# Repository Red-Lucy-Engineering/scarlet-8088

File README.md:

# "scarlet-8088": Intel 8088-based ATX motherboard

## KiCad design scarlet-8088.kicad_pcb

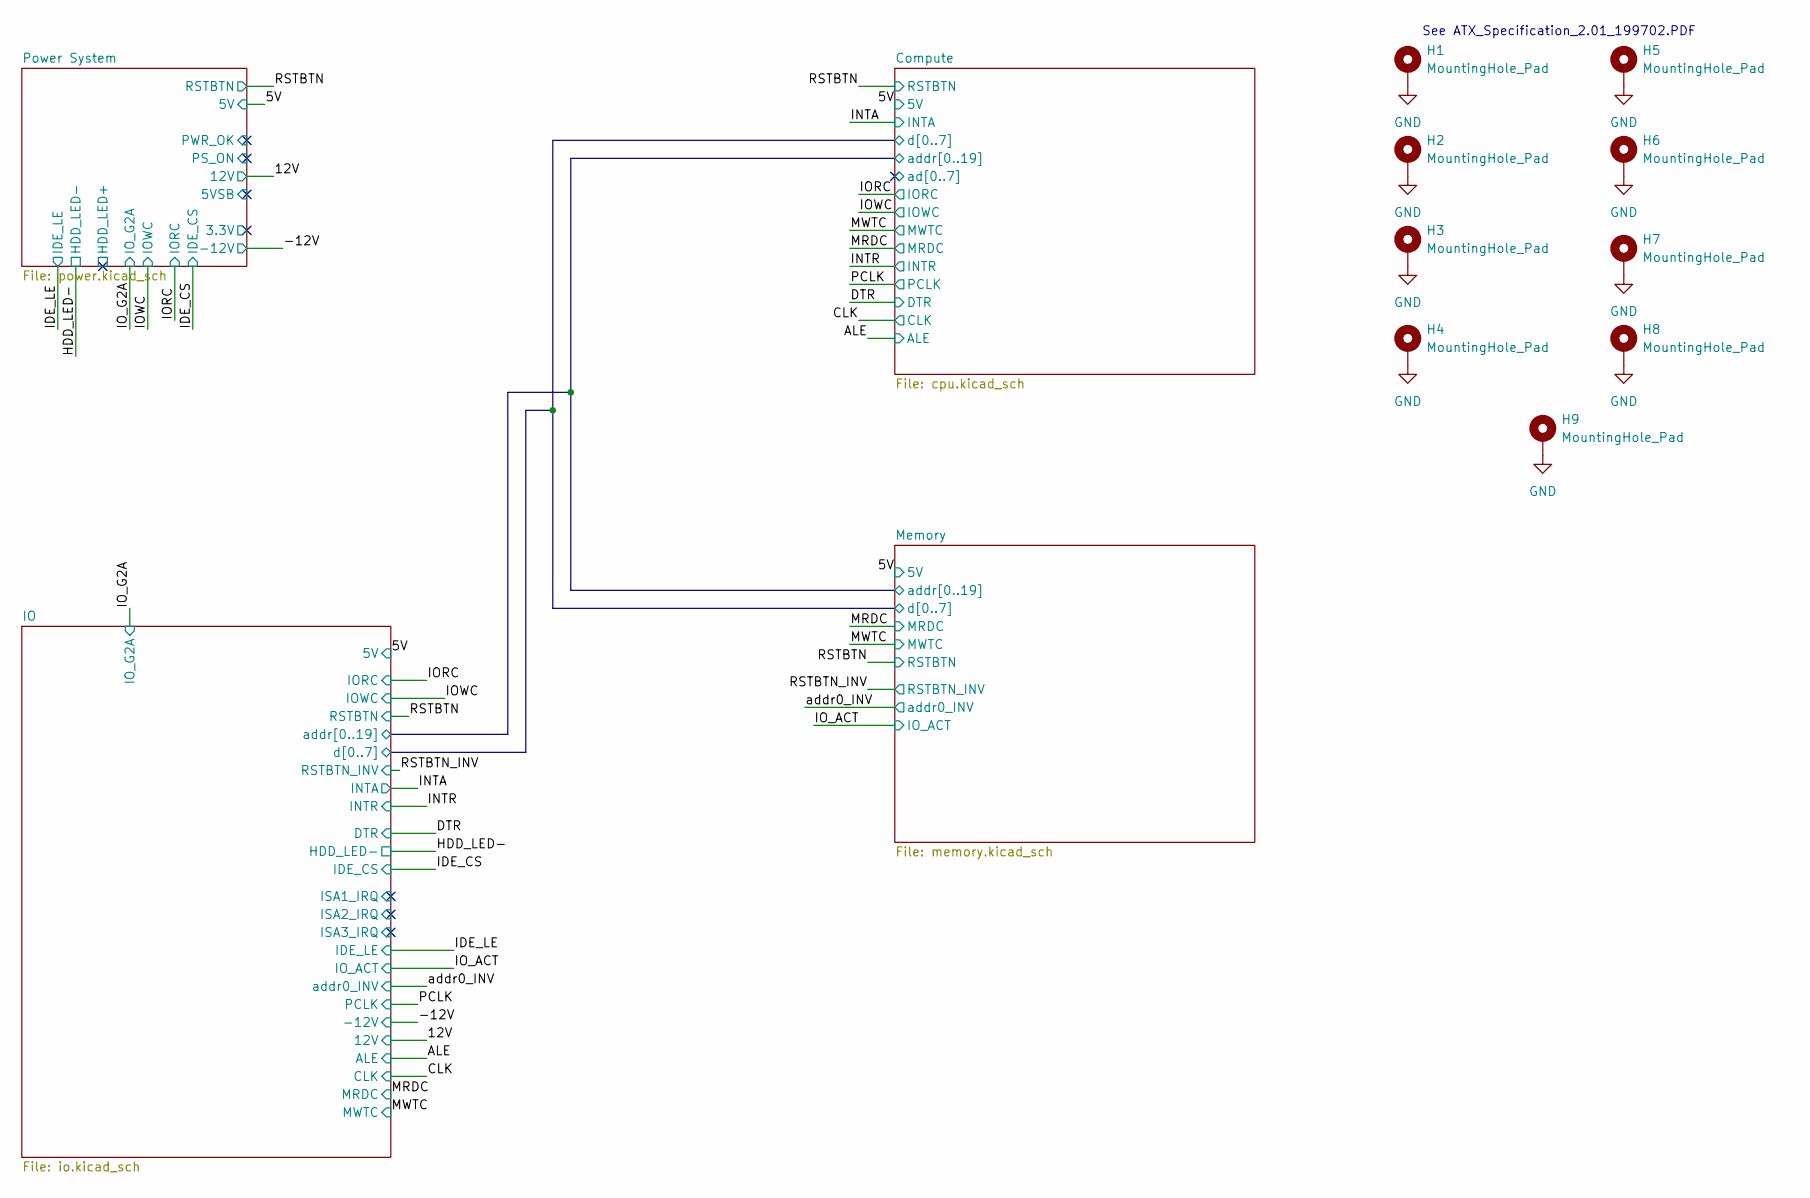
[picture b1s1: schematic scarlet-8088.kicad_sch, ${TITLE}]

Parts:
H1, H2, H3, H4, H5, H6, H7, H8, H9: MountingHole_Pad; MountingHole_3.2mm_M3_Pad_TopBottom

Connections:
GND: H1.1 (1_1), H2.1 (1_1), H3.1 (1_1), H4.1 (1_1), H5.1 (1_1), H6.1 (1_1), H7.1 (1_1), H8.1 (1_1), H9.1 (1_1); also elsewhere on the board

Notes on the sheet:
See ATX_Specification_2.01_199702.PDF

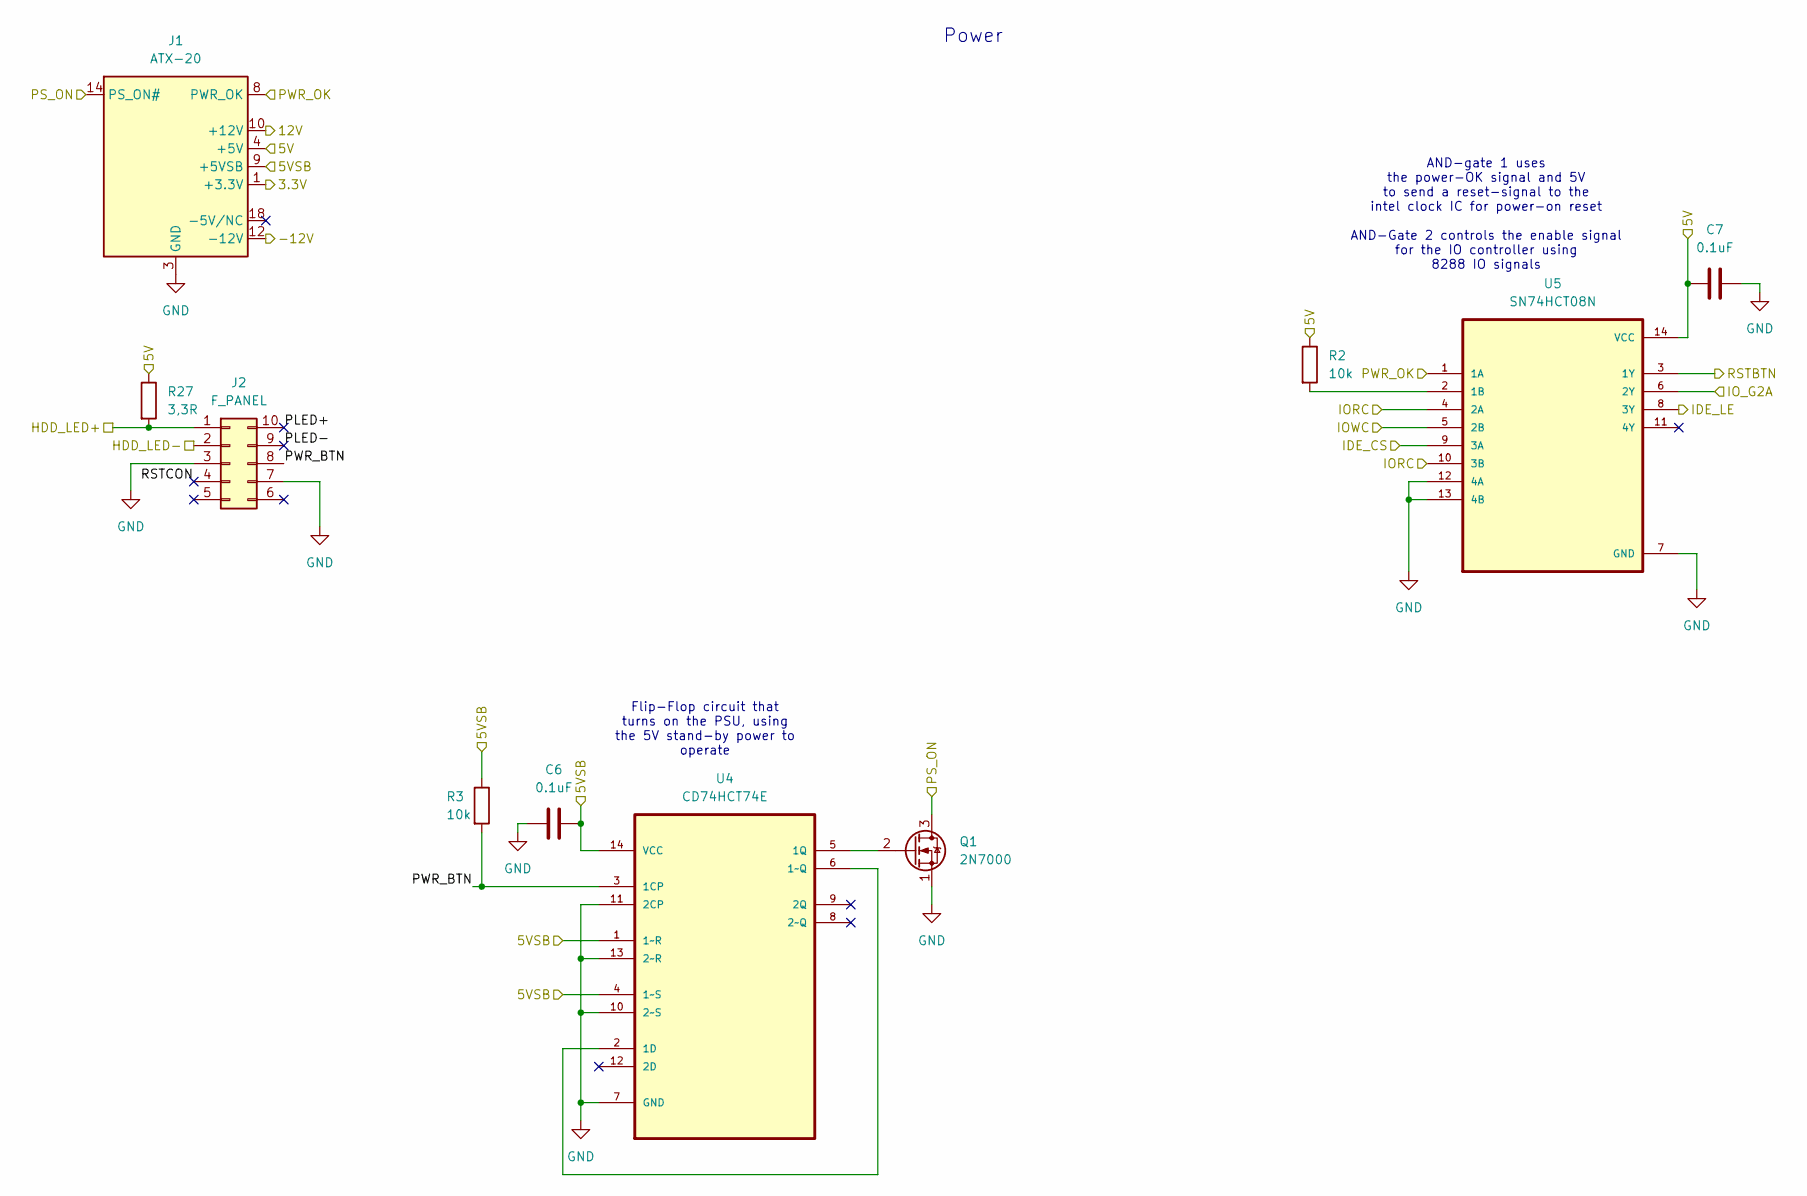
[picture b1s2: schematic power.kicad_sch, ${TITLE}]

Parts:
C6, C7: 0.1uF; C_Disc_D3.0mm_W1.6mm_P2.50mm
J1: ATX-20; Molex_Mini-Fit_Jr_5566-20A_2x10_P4.20mm_Vertical
J2: F_PANEL; PinHeader_2x05_P2.54mm_Vertical
Q1: 2N7000; TO-92_Inline
R2, R3: 10k; R_Axial_DIN0204_L3.6mm_D1.6mm_P5.08mm_Horizontal
R27: 3,3R; R_Axial_DIN0204_L3.6mm_D1.6mm_P5.08mm_Horizontal
U4: CD74HCT74E; DIP254P762X508-14; MPN CD74HCT74E
U5: SN74HCT08N; DIP794W45P254L1969H508Q14

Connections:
/5V: C7.1, J1.4 (+5V), J1.6 (+5V), J1.19 (+5V), J1.20 (+5V), R2.1, R27.1, U5.14 (VCC); also elsewhere on the board
/12V: J1.10 (+12V); also elsewhere on the board
/-12V: J1.12 (-12V); also elsewhere on the board
/HDD_LED-: J2.2; also elsewhere on the board
/IDE_CS: U5.9 (3A); also elsewhere on the board
/IDE_LE: U5.8 (3Y); also elsewhere on the board
/IORC: U5.4 (2A), U5.10 (3B); also elsewhere on the board
/IOWC: U5.5 (2B); also elsewhere on the board
/IO_G2A: U5.6 (2Y); also elsewhere on the board
/Power System/5VSB: C6.2, J1.9 (+5VSB), R3.1, U4.1 (1~R), U4.4 (1~S), U4.14 (VCC)
/Power System/HDD_LED+: J2.1, R27.2
/Power System/PLED+: J2.10
/Power System/PLED-: J2.9
/Power System/PS_ON: J1.14 (PS_ON#), Q1.3 (D)
/Power System/PWR_BTN: J2.8, R3.2, U4.3 (1CP)
/Power System/PWR_OK: J1.8 (PWR_OK), U5.1 (1A)
/Power System/RSTCON: J2.4
/RSTBTN: U5.3 (1Y); also elsewhere on the board
GND: C6.1, C7.2, J1.3 (GND), J1.5 (GND), J1.7 (GND), J1.13 (GND), J1.15 (GND), J1.16 (GND), J1.17 (GND), J2.3, J2.7, Q1.1 (S), U4.7 (GND), U4.10 (2~S), U4.11 (2CP), U4.13 (2~R), U5.7 (GND), U5.12 (4A), U5.13 (4B); also elsewhere on the board
unnamed: Q1.2 (G), U4.5 (1Q)
unnamed: U4.2 (1D), U4.6 (1~Q)
unnamed: R2.2, U5.2 (1B)

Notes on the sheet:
Power
AND-gate 1 uses the power-OK signal and 5V to send a reset-signal to the intel clock IC for power-on reset AND-Gate 2 controls the enable signal for the IO controller using 8288 IO signals
Flip-Flop circuit that turns on the PSU, using the 5V stand-by power to operate

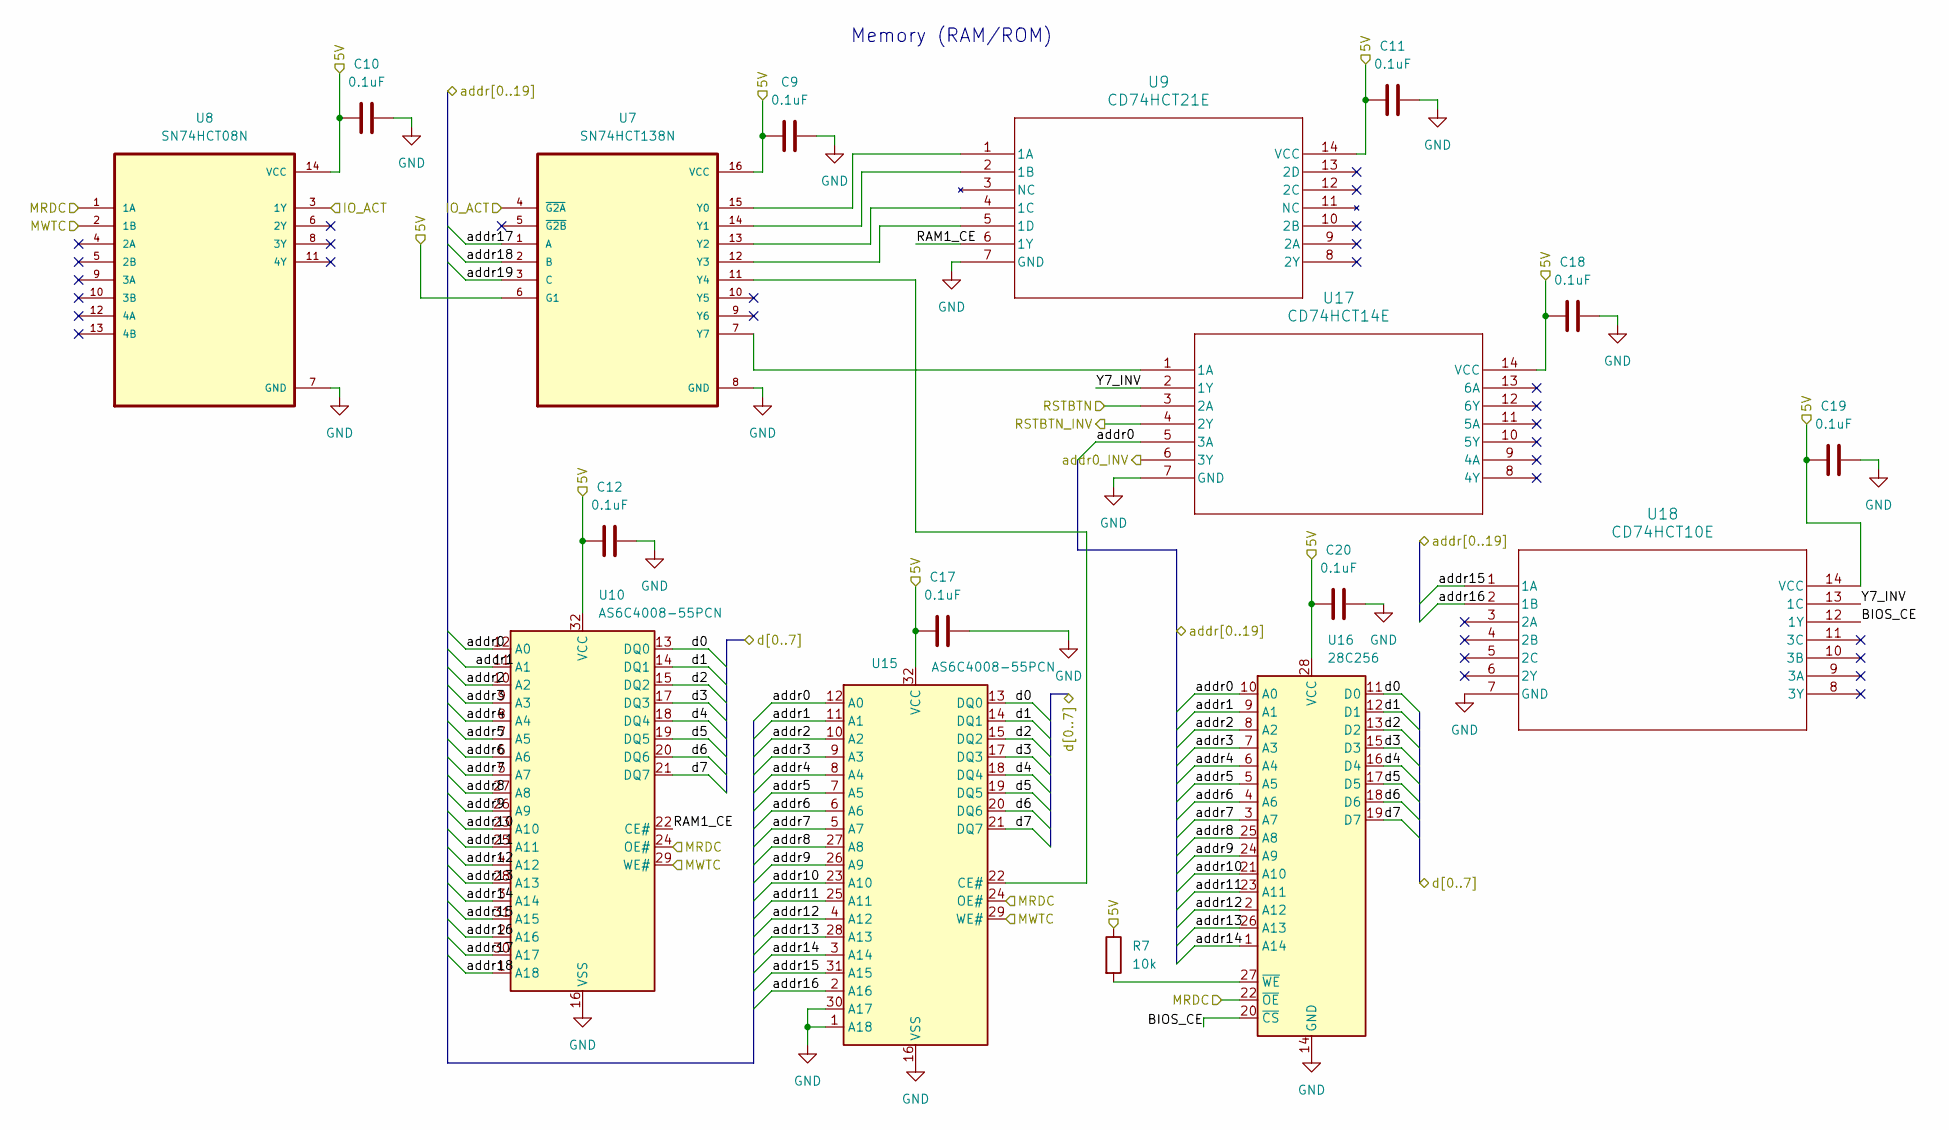
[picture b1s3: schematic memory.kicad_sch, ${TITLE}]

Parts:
C9, C10, C11, C12, C17, C18, C19, C20: 0.1uF; C_Disc_D3.0mm_W1.6mm_P2.50mm
R7: 10k; R_Axial_DIN0204_L3.6mm_D1.6mm_P5.08mm_Horizontal
U7: SN74HCT138N; DIP794W45P254L1969H508Q16
U8: SN74HCT08N; DIP794W45P254L1969H508Q14
U9: CD74HCT21E; N14
U10, U15: AS6C4008-55PCN; DIP-32_W15.24mm_Socket
U16: 28C256; DIP-28_W15.24mm_Socket
U17: CD74HCT14E
U18: CD74HCT10E; N14

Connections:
/5V: C9.2, C10.1, C11.2, C12.1, C17.1, C18.2, C19.2, C20.1, R7.1, U7.6 (G1), U7.16 (VCC), U8.14 (VCC), U9.14 (VCC), U10.32 (VCC), U15.32 (VCC), U16.28 (VCC), U17.14 (VCC), U18.14 (VCC); also elsewhere on the board
/Compute/addr0: U10.12 (A0), U15.12 (A0), U16.10 (A0), U17.5 (3A); also elsewhere on the board
/Compute/addr1: U10.11 (A1), U15.11 (A1), U16.9 (A1); also elsewhere on the board
/Compute/addr2: U10.10 (A2), U15.10 (A2), U16.8 (A2); also elsewhere on the board
/Compute/addr3: U10.9 (A3), U15.9 (A3), U16.7 (A3); also elsewhere on the board
/Compute/addr4: U10.8 (A4), U15.8 (A4), U16.6 (A4); also elsewhere on the board
/Compute/addr5: U10.7 (A5), U15.7 (A5), U16.5 (A5); also elsewhere on the board
/Compute/addr6: U10.6 (A6), U15.6 (A6), U16.4 (A6); also elsewhere on the board
/Compute/addr7: U10.5 (A7), U15.5 (A7), U16.3 (A7); also elsewhere on the board
/Compute/addr8: U10.27 (A8), U15.27 (A8), U16.25 (A8); also elsewhere on the board
/Compute/addr9: U10.26 (A9), U15.26 (A9), U16.24 (A9); also elsewhere on the board
/Compute/addr10: U10.23 (A10), U15.23 (A10), U16.21 (A10); also elsewhere on the board
/Compute/addr11: U10.25 (A11), U15.25 (A11), U16.23 (A11); also elsewhere on the board
/Compute/addr12: U10.4 (A12), U15.4 (A12), U16.2 (A12); also elsewhere on the board
/Compute/addr13: U10.28 (A13), U15.28 (A13), U16.26 (A13); also elsewhere on the board
/Compute/addr14: U10.3 (A14), U15.3 (A14), U16.1 (A14); also elsewhere on the board
/Compute/addr15: U10.31 (A15), U15.31 (A15), U18.1 (1A); also elsewhere on the board
/Compute/addr16: U10.2 (A16), U15.2 (A16), U18.2 (1B); also elsewhere on the board
/Compute/addr17: U7.1 (A), U10.30 (A17); also elsewhere on the board
/Compute/addr18: U7.2 (B), U10.1 (A18); also elsewhere on the board
/Compute/addr19: U7.3 (C); also elsewhere on the board
/Compute/d0: U10.13 (DQ0), U15.13 (DQ0), U16.11 (D0); also elsewhere on the board
/Compute/d1: U10.14 (DQ1), U15.14 (DQ1), U16.12 (D1); also elsewhere on the board
/Compute/d2: U10.15 (DQ2), U15.15 (DQ2), U16.13 (D2); also elsewhere on the board
/Compute/d3: U10.17 (DQ3), U15.17 (DQ3), U16.15 (D3); also elsewhere on the board
/Compute/d4: U10.18 (DQ4), U15.18 (DQ4), U16.16 (D4); also elsewhere on the board
/Compute/d5: U10.19 (DQ5), U15.19 (DQ5), U16.17 (D5); also elsewhere on the board
/Compute/d6: U10.20 (DQ6), U15.20 (DQ6), U16.18 (D6); also elsewhere on the board
/Compute/d7: U10.21 (DQ7), U15.21 (DQ7), U16.19 (D7); also elsewhere on the board
/IO_ACT: U7.4 (~G2A), U8.3 (1Y); also elsewhere on the board
/MRDC: U8.1 (1A), U10.24 (OE#), U15.24 (OE#), U16.22 (~OE); also elsewhere on the board
/MWTC: U8.2 (1B), U10.29 (WE#), U15.29 (WE#); also elsewhere on the board
/Memory/BIOS_CE: U16.20 (~CS), U18.12 (1Y)
/Memory/RAM1_CE: U9.6 (1Y), U10.22 (CE#)
/Memory/Y7_INV: U17.2 (1Y), U18.13 (1C)
/RSTBTN: U17.3 (2A); also elsewhere on the board
/RSTBTN_INV: U17.4 (2Y); also elsewhere on the board
/addr0_INV: U17.6 (3Y); also elsewhere on the board
GND: C9.1, C10.2, C11.1, C12.2, C17.2, C18.1, C19.1, C20.2, U7.8 (GND), U8.7 (GND), U9.7 (GND), U10.16 (VSS), U15.1 (A18), U15.16 (VSS), U15.30 (A17), U16.14 (GND), U17.7 (GND), U18.7 (GND); also elsewhere on the board
unnamed: U7.15 (Y0), U9.1 (1A)
unnamed: U7.14 (Y1), U9.2 (1B)
unnamed: U7.13 (Y2), U9.4 (1C)
unnamed: U7.12 (Y3), U9.5 (1D)
unnamed: U7.11 (Y4), U15.22 (CE#)
unnamed: R7.2, U16.27 (~WE)
unnamed: U7.7 (Y7), U17.1 (1A)

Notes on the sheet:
Memory (RAM/ROM)

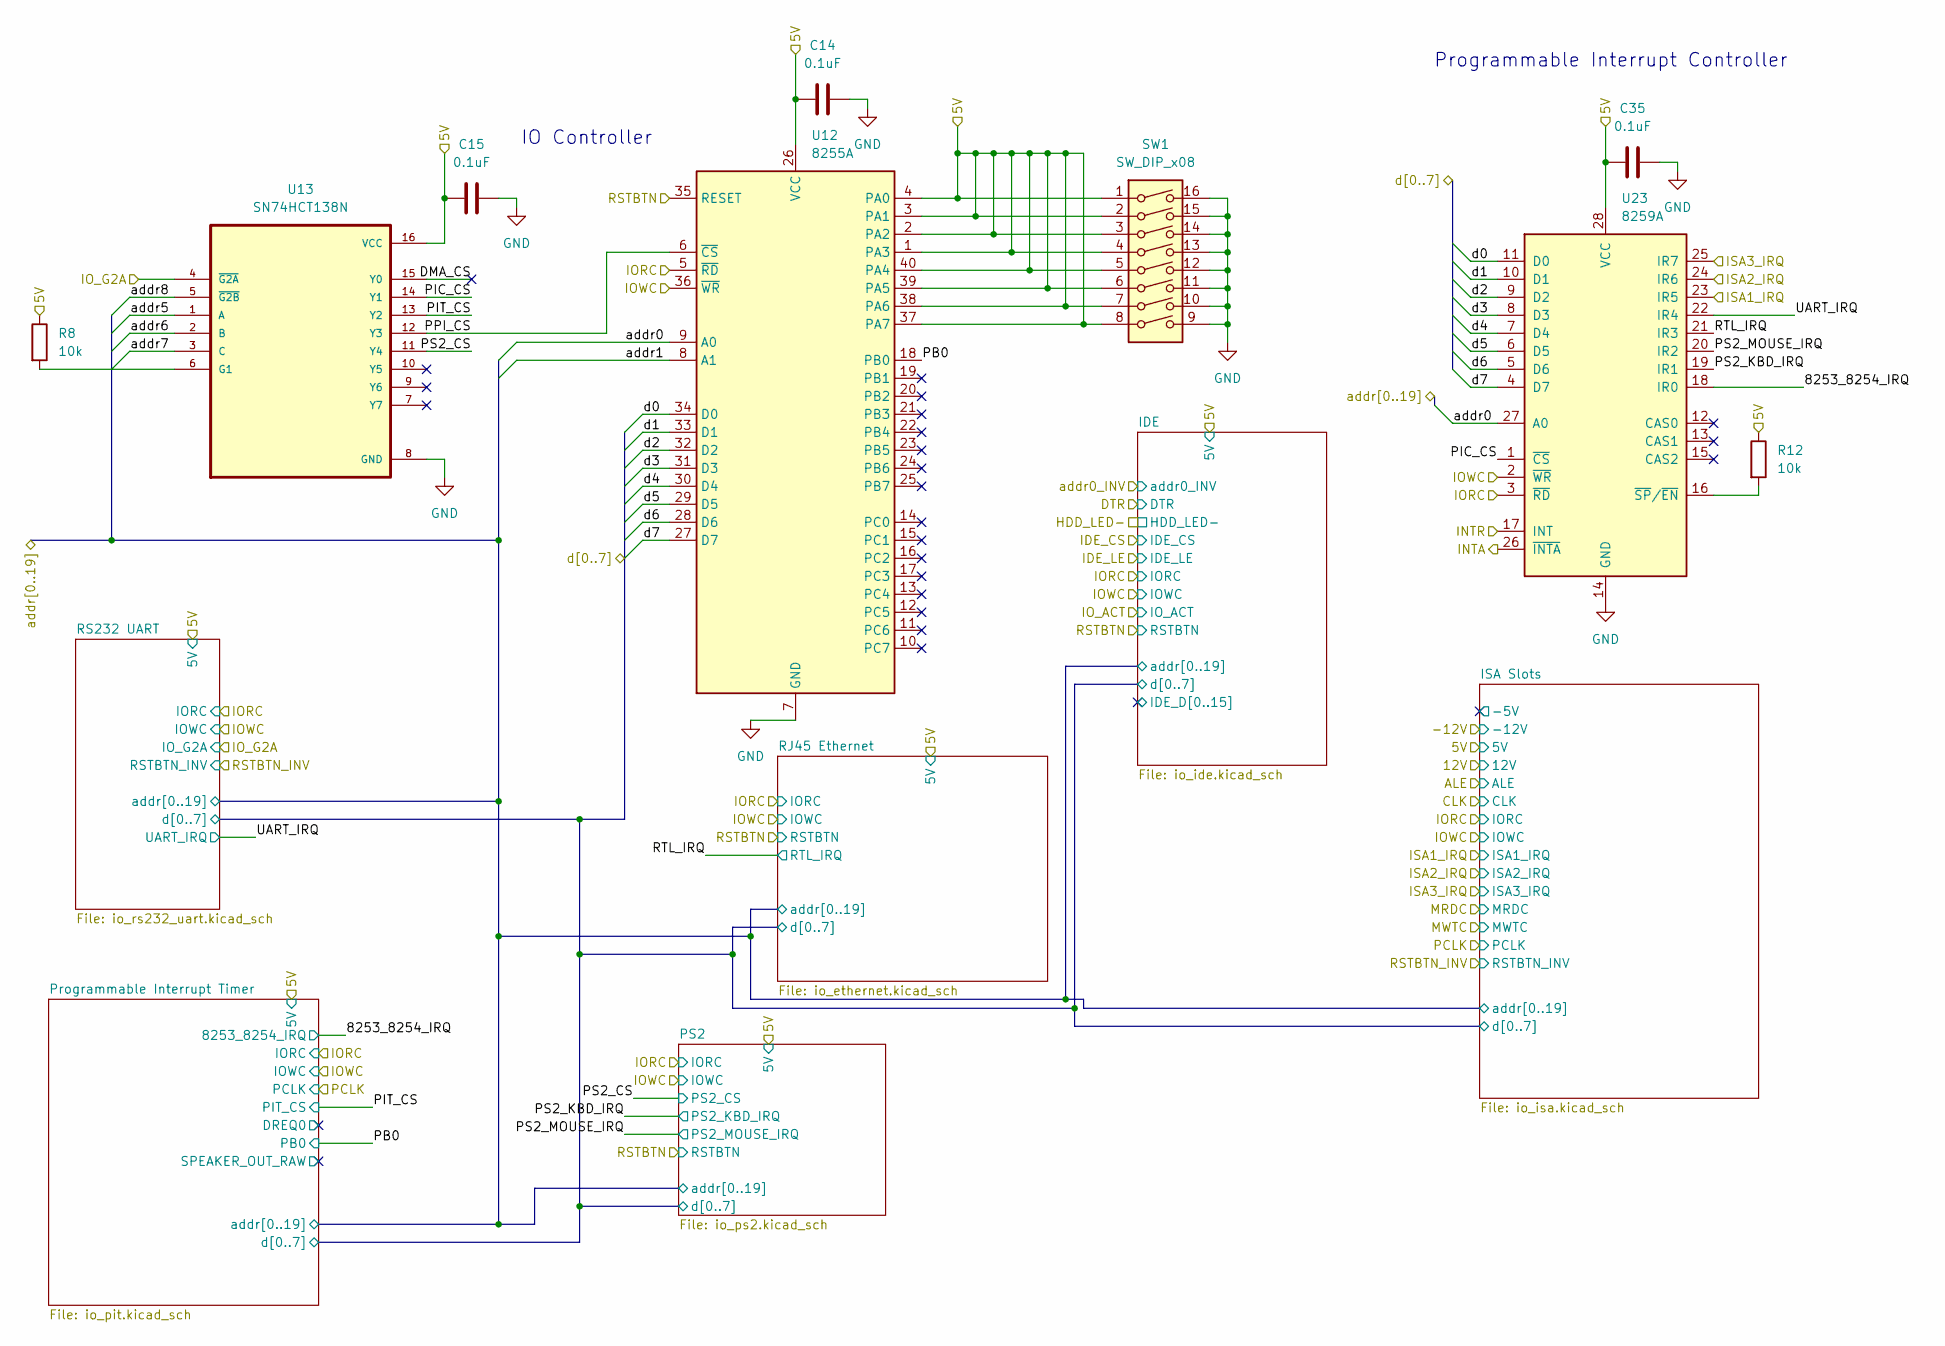
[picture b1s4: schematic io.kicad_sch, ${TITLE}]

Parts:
C14, C15, C35: 0.1uF; C_Disc_D3.0mm_W1.6mm_P2.50mm
R8, R12: 10k; R_Axial_DIN0204_L3.6mm_D1.6mm_P5.08mm_Horizontal
SW1: SW_DIP_x08; SW_DIP_SPSTx08_Piano_10.8x21.88mm_W7.62mm_P2.54mm
U12: 8255A; DIP-40_W15.24mm_Socket
U13: SN74HCT138N; DIP794W45P254L1969H508Q16
U23: 8259A; DIP-28_W15.24mm_Socket

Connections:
/5V: C14.1, C15.1, C35.1, R8.1, R12.1, SW1.1, SW1.2, SW1.3, SW1.4, SW1.5, SW1.6, SW1.7, SW1.8, U12.1 (PA3), U12.2 (PA2), U12.3 (PA1), U12.4 (PA0), U12.26 (VCC), U12.37 (PA7), U12.38 (PA6), U12.39 (PA5), U12.40 (PA4), U13.16 (VCC), U23.28 (VCC); also elsewhere on the board
/Compute/addr0: U12.9 (A0), U23.27 (A0); also elsewhere on the board
/Compute/addr1: U12.8 (A1); also elsewhere on the board
/Compute/addr5: U13.1 (A); also elsewhere on the board
/Compute/addr6: U13.2 (B); also elsewhere on the board
/Compute/addr7: U13.3 (C); also elsewhere on the board
/Compute/addr8: U13.5 (~G2B); also elsewhere on the board
/Compute/d0: U12.34 (D0), U23.11 (D0); also elsewhere on the board
/Compute/d1: U12.33 (D1), U23.10 (D1); also elsewhere on the board
/Compute/d2: U12.32 (D2), U23.9 (D2); also elsewhere on the board
/Compute/d3: U12.31 (D3), U23.8 (D3); also elsewhere on the board
/Compute/d4: U12.30 (D4), U23.7 (D4); also elsewhere on the board
/Compute/d5: U12.29 (D5), U23.6 (D5); also elsewhere on the board
/Compute/d6: U12.28 (D6), U23.5 (D6); also elsewhere on the board
/Compute/d7: U12.27 (D7), U23.4 (D7); also elsewhere on the board
/INTA: U23.26 (~INTA); also elsewhere on the board
/INTR: U23.17 (INT); also elsewhere on the board
/IO/8253_8254_IRQ: U23.18 (IR0); also elsewhere on the board
/IO/DMA_CS: U13.15 (Y0)
/IO/ISA1_IRQ: U23.23 (IR5); also elsewhere on the board
/IO/ISA2_IRQ: U23.24 (IR6); also elsewhere on the board
/IO/ISA3_IRQ: U23.25 (IR7); also elsewhere on the board
/IO/PB0: U12.18 (PB0); also elsewhere on the board
/IO/PIC_CS: U13.14 (Y1), U23.1 (~CS)
/IO/PIT_CS: U13.13 (Y2); also elsewhere on the board
/IO/PPI_CS: U12.6 (~CS), U13.12 (Y3)
/IO/PS2_CS: U13.11 (Y4); also elsewhere on the board
/IO/PS2_KBD_IRQ: U23.19 (IR1); also elsewhere on the board
/IO/PS2_MOUSE_IRQ: U23.20 (IR2); also elsewhere on the board
/IO/RTL_IRQ: U23.21 (IR3); also elsewhere on the board
/IO/UART_IRQ: U23.22 (IR4); also elsewhere on the board
/IORC: U12.5 (~RD), U23.3 (~RD); also elsewhere on the board
/IOWC: U12.36 (~WR), U23.2 (~WR); also elsewhere on the board
/IO_G2A: U13.4 (~G2A); also elsewhere on the board
/RSTBTN: U12.35 (RESET); also elsewhere on the board
GND: C14.2, C15.2, C35.2, SW1.9, SW1.10, SW1.11, SW1.12, SW1.13, SW1.14, SW1.15, SW1.16, U12.7 (GND), U13.8 (GND), U23.14 (GND); also elsewhere on the board
unnamed: R8.2, U13.6 (G1)
unnamed: R12.2, U23.16 (~SP/~EN)

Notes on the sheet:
Programmable Interrupt Controller
IO Controller

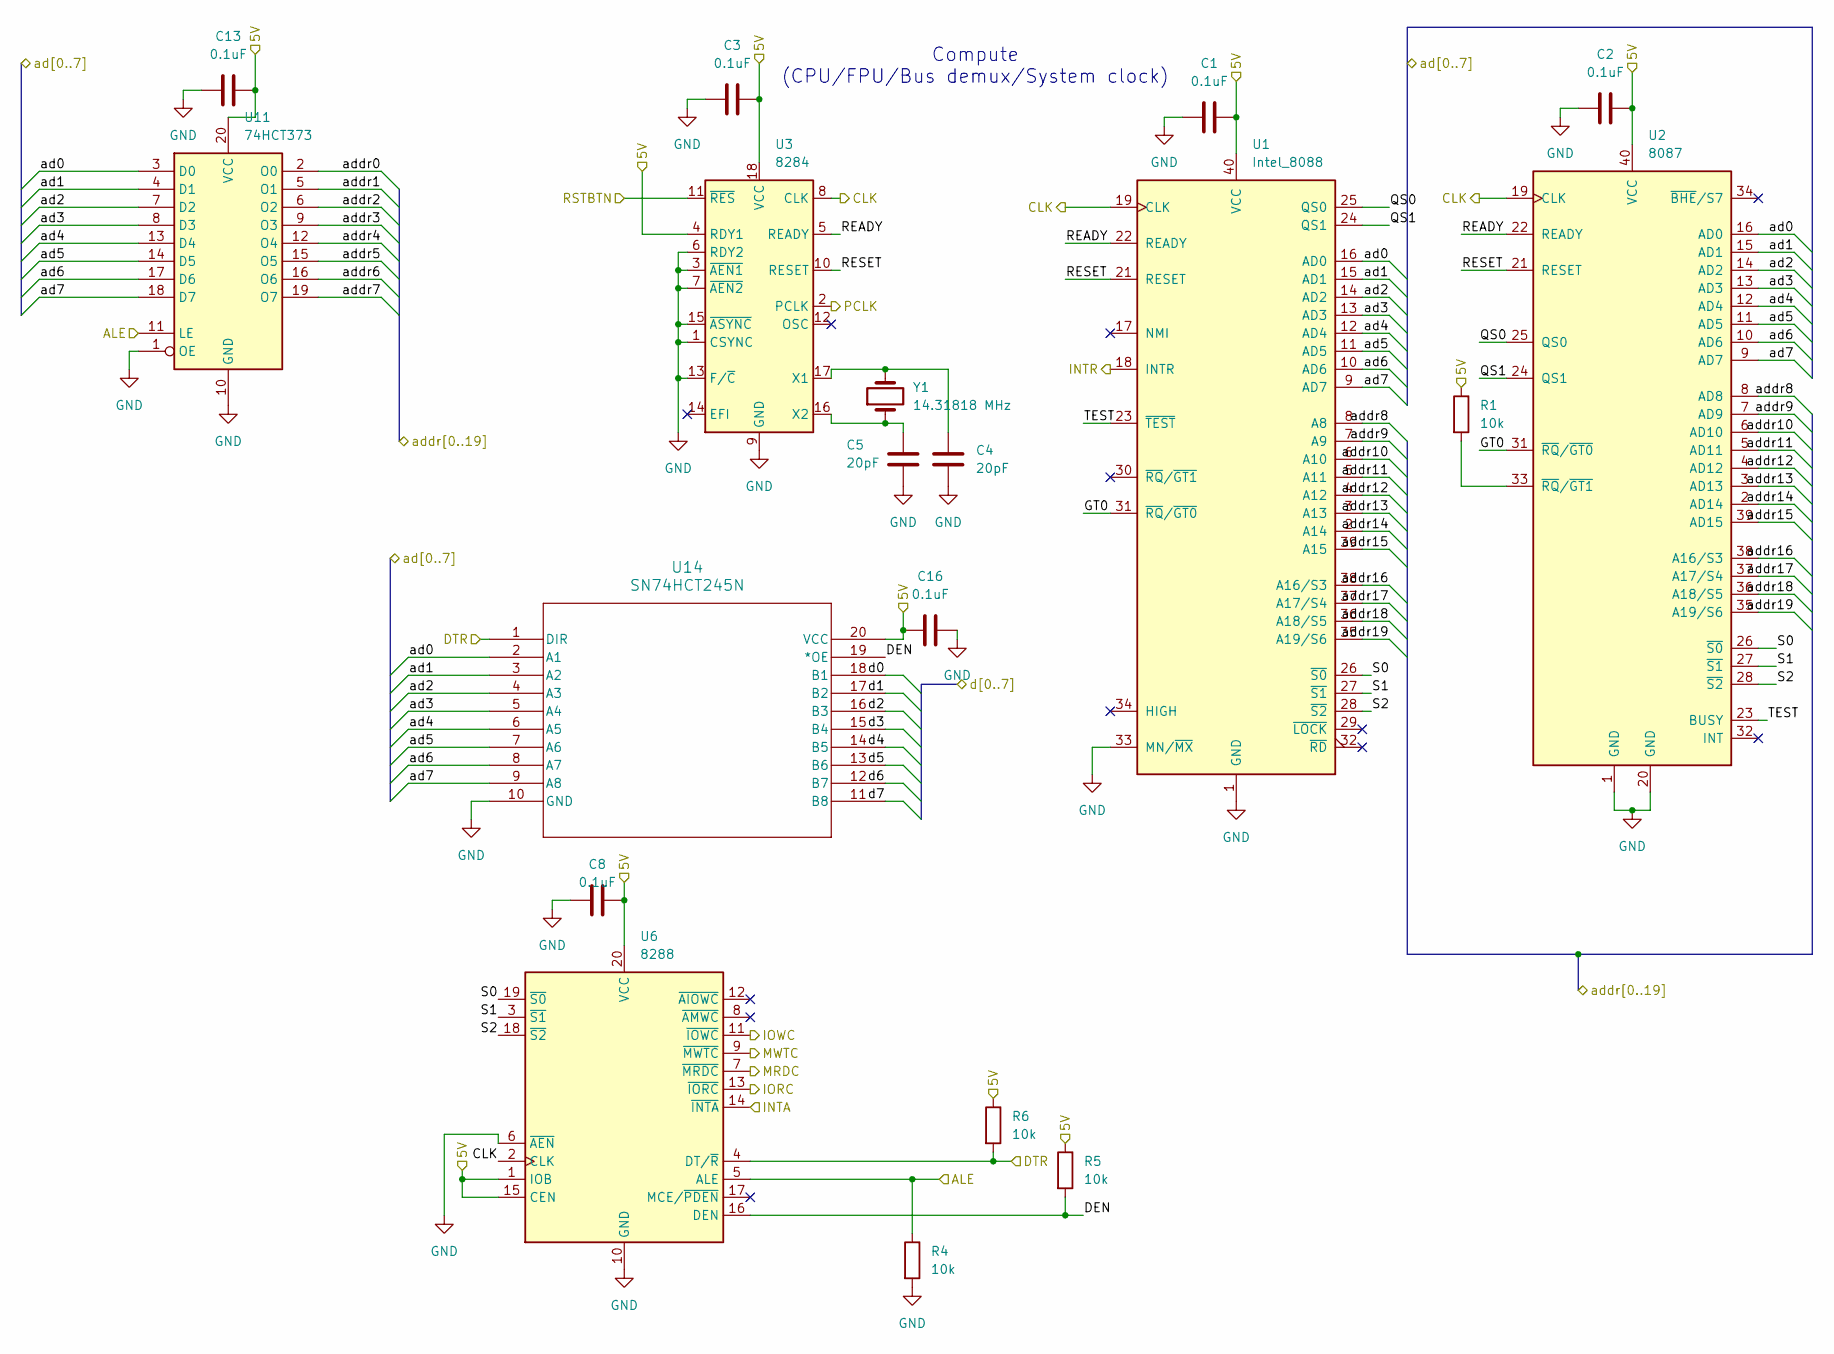
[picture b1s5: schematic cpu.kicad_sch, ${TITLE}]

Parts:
C1, C2, C3, C8, C13, C16: 0.1uF; C_Disc_D3.0mm_W1.6mm_P2.50mm
C4, C5: 20pF; C_Disc_D3.0mm_W1.6mm_P2.50mm
R1, R4, R5, R6: 10k; R_Axial_DIN0204_L3.6mm_D1.6mm_P5.08mm_Horizontal
U1: Intel_8088; DIP-40_W15.24mm_Socket
U2: 8087; DIP-40_W15.24mm_Socket
U3: 8284; DIP-18_W7.62mm_Socket
U6: 8288; DIP-20_W7.62mm_Socket
U11: 74HCT373; DIP-20_W7.62mm_Socket
U14: SN74HCT245N
Y1: 14.31818 MHz; Crystal_HC49-U_Vertical

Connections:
/5V: C1.2, C2.2, C3.2, C8.2, C13.2, C16.2, R1.1, R5.1, R6.1, U1.40 (VCC), U2.40 (VCC), U3.4 (RDY1), U3.18 (VCC), U6.1 (IOB), U6.15 (CEN), U6.20 (VCC), U11.20 (VCC), U14.20 (VCC); also elsewhere on the board
/ALE: R4.1, U6.5 (ALE), U11.11 (LE); also elsewhere on the board
/CLK: U1.19 (CLK), U2.19 (CLK), U3.8 (CLK), U6.2 (CLK); also elsewhere on the board
/Compute/DEN: R5.2, U6.16 (DEN), U14.19 (*OE)
/Compute/GT0: U1.31 (~RQ/~GT0), U2.31 (~RQ/~GT0)
/Compute/QS0: U1.25 (QS0), U2.25 (QS0)
/Compute/QS1: U1.24 (QS1), U2.24 (QS1)
/Compute/READY: U1.22 (READY), U2.22 (READY), U3.5 (READY)
/Compute/RESET: U1.21 (RESET), U2.21 (RESET), U3.10 (RESET)
/Compute/S0: U1.26 (~S0), U2.26 (~S0), U6.19 (~S0)
/Compute/S1: U1.27 (~S1), U2.27 (~S1), U6.3 (~S1)
/Compute/S2: U1.28 (~S2), U2.28 (~S2), U6.18 (~S2)
/Compute/TEST: U1.23 (~TEST), U2.23 (BUSY)
/Compute/ad0: U1.16 (AD0), U2.16 (AD0), U11.3 (D0), U14.2 (A1)
/Compute/ad1: U1.15 (AD1), U2.15 (AD1), U11.4 (D1), U14.3 (A2)
/Compute/ad2: U1.14 (AD2), U2.14 (AD2), U11.7 (D2), U14.4 (A3)
/Compute/ad3: U1.13 (AD3), U2.13 (AD3), U11.8 (D3), U14.5 (A4)
/Compute/ad4: U1.12 (AD4), U2.12 (AD4), U11.13 (D4), U14.6 (A5)
/Compute/ad5: U1.11 (AD5), U2.11 (AD5), U11.14 (D5), U14.7 (A6)
/Compute/ad6: U1.10 (AD6), U2.10 (AD6), U11.17 (D6), U14.8 (A7)
/Compute/ad7: U1.9 (AD7), U2.9 (AD7), U11.18 (D7), U14.9 (A8)
/Compute/addr0: U11.2 (O0); also elsewhere on the board
/Compute/addr1: U11.5 (O1); also elsewhere on the board
/Compute/addr2: U11.6 (O2); also elsewhere on the board
/Compute/addr3: U11.9 (O3); also elsewhere on the board
/Compute/addr4: U11.12 (O4); also elsewhere on the board
/Compute/addr5: U11.15 (O5); also elsewhere on the board
/Compute/addr6: U11.16 (O6); also elsewhere on the board
/Compute/addr7: U11.19 (O7); also elsewhere on the board
/Compute/addr8: U1.8 (A8), U2.8 (AD8); also elsewhere on the board
/Compute/addr9: U1.7 (A9), U2.7 (AD9); also elsewhere on the board
/Compute/addr10: U1.6 (A10), U2.6 (AD10); also elsewhere on the board
/Compute/addr11: U1.5 (A11), U2.5 (AD11); also elsewhere on the board
/Compute/addr12: U1.4 (A12), U2.4 (AD12); also elsewhere on the board
/Compute/addr13: U1.3 (A13), U2.3 (AD13); also elsewhere on the board
/Compute/addr14: U1.2 (A14), U2.2 (AD14); also elsewhere on the board
/Compute/addr15: U1.39 (A15), U2.39 (AD15); also elsewhere on the board
/Compute/addr16: U1.38 (A16/S3), U2.38 (A16/S3); also elsewhere on the board
/Compute/addr17: U1.37 (A17/S4), U2.37 (A17/S4); also elsewhere on the board
/Compute/addr18: U1.36 (A18/S5), U2.36 (A18/S5); also elsewhere on the board
/Compute/addr19: U1.35 (A19/S6), U2.35 (A19/S6); also elsewhere on the board
/Compute/d0: U14.18 (B1); also elsewhere on the board
/Compute/d1: U14.17 (B2); also elsewhere on the board
/Compute/d2: U14.16 (B3); also elsewhere on the board
/Compute/d3: U14.15 (B4); also elsewhere on the board
/Compute/d4: U14.14 (B5); also elsewhere on the board
/Compute/d5: U14.13 (B6); also elsewhere on the board
/Compute/d6: U14.12 (B7); also elsewhere on the board
/Compute/d7: U14.11 (B8); also elsewhere on the board
/DTR: R6.2, U6.4 (DT/~R), U14.1 (DIR); also elsewhere on the board
/INTA: U6.14 (~INTA); also elsewhere on the board
/INTR: U1.18 (INTR); also elsewhere on the board
/IORC: U6.13 (~IORC); also elsewhere on the board
/IOWC: U6.11 (~IOWC); also elsewhere on the board
/MRDC: U6.7 (~MRDC); also elsewhere on the board
/MWTC: U6.9 (~MWTC); also elsewhere on the board
/PCLK: U3.2 (PCLK); also elsewhere on the board
/RSTBTN: U3.11 (~RES); also elsewhere on the board
GND: C1.1, C2.1, C3.1, C4.1, C5.2, C8.1, C13.1, C16.1, R4.2, U1.1 (GND), U1.20 (GND), U1.33 (MN/~MX), U2.1 (GND), U2.20 (GND), U3.1 (CSYNC), U3.3 (~AEN1), U3.6 (RDY2), U3.7 (~AEN2), U3.9 (GND), U3.13 (F/~C), U3.15 (~ASYNC), U6.6 (~AEN), U6.10 (GND), U11.1 (OE), U11.10 (GND), U14.10 (GND); also elsewhere on the board
unnamed: R1.2, U2.33 (~RQ/~GT1)
unnamed: C4.2, U3.17 (X1), Y1.2
unnamed: C5.1, U3.16 (X2), Y1.1

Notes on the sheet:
Compute (CPU/FPU/Bus demux/System clock)

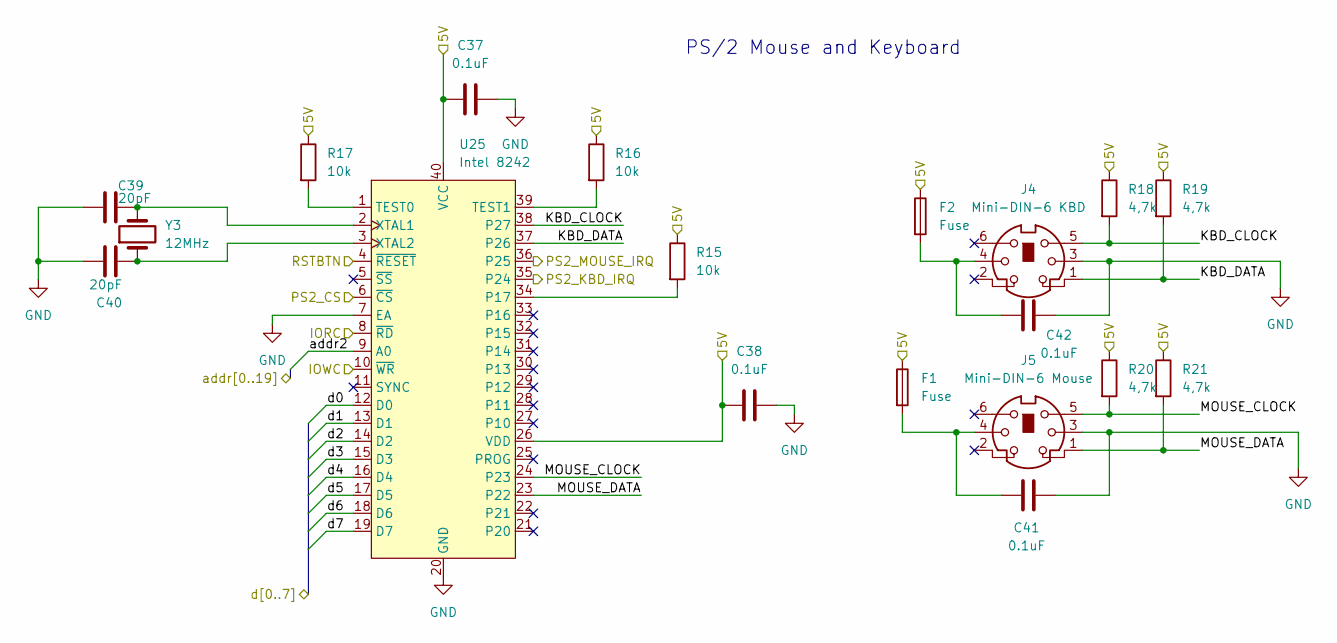
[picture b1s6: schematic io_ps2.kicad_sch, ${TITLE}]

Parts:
C37, C38, C41, C42: 0.1uF; C_Disc_D3.0mm_W1.6mm_P2.50mm
C39, C40: 20pF; C_Disc_D3.0mm_W1.6mm_P2.50mm
F1, F2: Fuse; Fuseholder_Clip-5x20mm_Eaton_1A5601-01_Inline_P20.80x6.76mm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
J4: Mini-DIN-6 KBD; minidin_6_ps2_pcb_mount
J5: Mini-DIN-6 Mouse; minidin_6_ps2_pcb_mount
R15, R16, R17: 10k; R_Axial_DIN0204_L3.6mm_D1.6mm_P5.08mm_Horizontal
R18, R19, R20, R21: 4,7k; R_Axial_DIN0204_L3.6mm_D1.6mm_P5.08mm_Horizontal
U25: Intel 8242; DIP-40_W15.24mm_Socket
Y3: 12MHz; Crystal_HC49-U_Vertical

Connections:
/5V: C37.1, C38.1, F1.1, F2.1, R15.1, R16.1, R17.1, R18.1, R19.1, R20.1, R21.1, U25.26 (VDD), U25.40 (VCC); also elsewhere on the board
/Compute/addr2: U25.9 (A0); also elsewhere on the board
/Compute/d0: U25.12 (D0); also elsewhere on the board
/Compute/d1: U25.13 (D1); also elsewhere on the board
/Compute/d2: U25.14 (D2); also elsewhere on the board
/Compute/d3: U25.15 (D3); also elsewhere on the board
/Compute/d4: U25.16 (D4); also elsewhere on the board
/Compute/d5: U25.17 (D5); also elsewhere on the board
/Compute/d6: U25.18 (D6); also elsewhere on the board
/Compute/d7: U25.19 (D7); also elsewhere on the board
/IO/PS2/KBD_CLOCK: J4.5, R18.2, U25.38 (P27)
/IO/PS2/KBD_DATA: J4.1, R19.2, U25.37 (P26)
/IO/PS2/MOUSE_CLOCK: J5.5, R20.2, U25.24 (P23)
/IO/PS2/MOUSE_DATA: J5.1, R21.2, U25.23 (P22)
/IO/PS2_CS: U25.6 (~CS); also elsewhere on the board
/IO/PS2_KBD_IRQ: U25.35 (P24); also elsewhere on the board
/IO/PS2_MOUSE_IRQ: U25.36 (P25); also elsewhere on the board
/IORC: U25.8 (~RD); also elsewhere on the board
/IOWC: U25.10 (~WR); also elsewhere on the board
/RSTBTN: U25.4 (~RESET); also elsewhere on the board
GND: C37.2, C38.2, C39.1, C40.1, C41.1, C42.1, J4.3, J5.3, U25.7 (EA), U25.20 (GND); also elsewhere on the board
unnamed: C41.2, F1.2, J5.4
unnamed: C42.2, F2.2, J4.4
unnamed: R15.2, U25.34 (P17)
unnamed: R17.2, U25.1 (TEST0)
unnamed: R16.2, U25.39 (TEST1)
unnamed: C39.2, U25.2 (XTAL1), Y3.2
unnamed: C40.2, U25.3 (XTAL2), Y3.1

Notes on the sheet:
PS/2 Mouse and Keyboard
